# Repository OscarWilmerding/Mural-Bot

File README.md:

# Mural Bot
 Mural Painting Robot

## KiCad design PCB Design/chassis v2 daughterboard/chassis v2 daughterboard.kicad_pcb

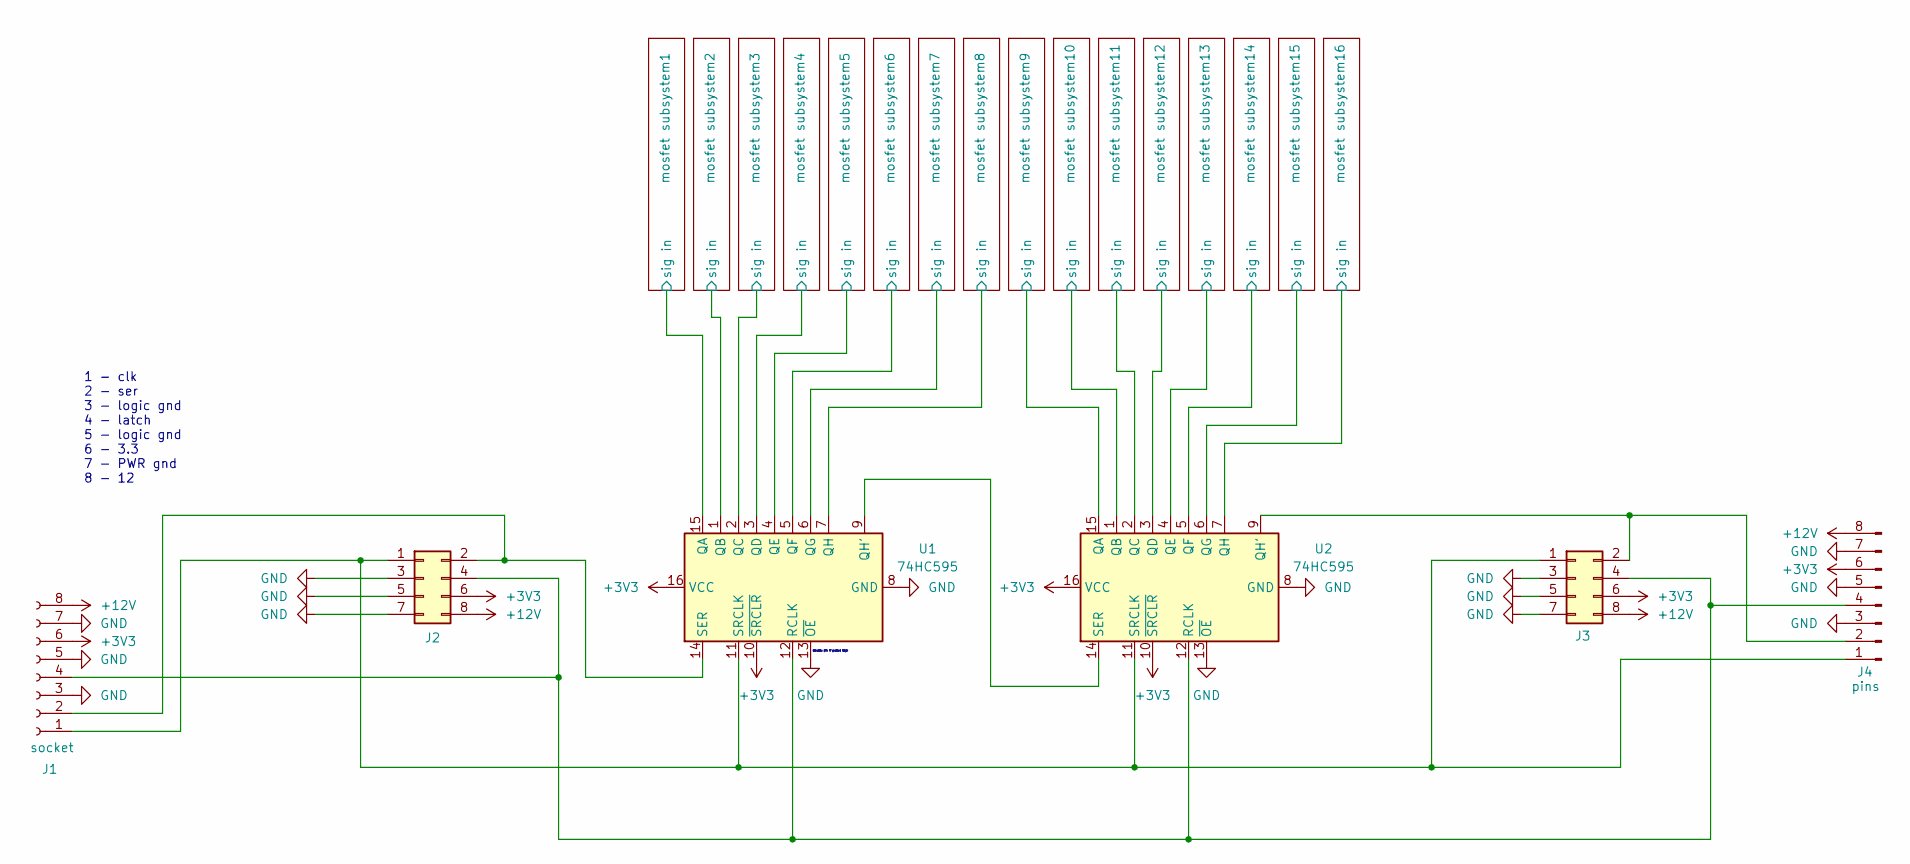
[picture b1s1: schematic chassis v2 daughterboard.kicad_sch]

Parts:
J1: socket; reversed socket connector
J2, J3: Conn_02x04_Odd_Even; PinHeader_2x04_P2.54mm_Vertical
J4: pins; reversed pin connector
U1, U2: 74HC595; DIP254P762X420-16

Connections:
+3V3: J1.6, J2.6, J3.6, J4.6, U1.10 (~SRCLR), U1.16 (VCC), U2.10 (~SRCLR), U2.16 (VCC)
+12V: J1.8, J2.8, J3.8, J4.8; also elsewhere on the board
/mosfet subsystem1/sig in: U1.15 (QA); also elsewhere on the board
/mosfet subsystem2/sig in: U1.1 (QB); also elsewhere on the board
/mosfet subsystem3/sig in: U1.2 (QC); also elsewhere on the board
/mosfet subsystem4/sig in: U1.3 (QD); also elsewhere on the board
/mosfet subsystem5/sig in: U1.4 (QE); also elsewhere on the board
/mosfet subsystem6/sig in: U1.5 (QF); also elsewhere on the board
/mosfet subsystem7/sig in: U1.6 (QG); also elsewhere on the board
/mosfet subsystem8/sig in: U1.7 (QH); also elsewhere on the board
/mosfet subsystem9/sig in: U2.15 (QA); also elsewhere on the board
/mosfet subsystem10/sig in: U2.1 (QB); also elsewhere on the board
/mosfet subsystem11/sig in: U2.2 (QC); also elsewhere on the board
/mosfet subsystem12/sig in: U2.3 (QD); also elsewhere on the board
/mosfet subsystem13/sig in: U2.4 (QE); also elsewhere on the board
/mosfet subsystem14/sig in: U2.5 (QF); also elsewhere on the board
/mosfet subsystem15/sig in: U2.6 (QG); also elsewhere on the board
/mosfet subsystem16/sig in: U2.7 (QH); also elsewhere on the board
GND: J1.3, J1.5, J1.7, J2.3, J2.5, J2.7, J3.3, J3.5, J3.7, J4.3, J4.5, J4.7, U1.8 (GND), U1.13 (~OE), U2.8 (GND), U2.13 (~OE); also elsewhere on the board
unnamed: J1.1, J2.1, J3.1, J4.1, U1.11 (SRCLK), U2.11 (SRCLK)
unnamed: J1.2, J2.2, U1.14 (SER)
unnamed: J1.4, J2.4, J3.4, J4.4, U1.12 (RCLK), U2.12 (RCLK)
unnamed: J3.2, J4.2, U2.9 (QH')
unnamed: U1.9 (QH'), U2.14 (SER)

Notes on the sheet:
1 - clk 2 - ser 3 - logic gnd 4 - latch 5 - logic gnd 6 - 3.3 7 - PWR gnd 8 - 12
disable pin if pulled high

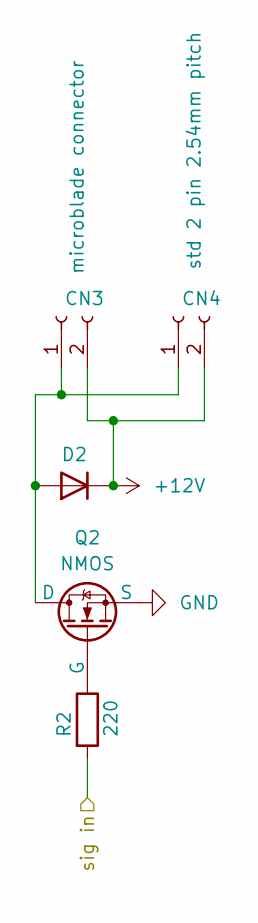
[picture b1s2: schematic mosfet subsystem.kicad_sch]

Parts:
CN3: microblade connector; modified jst zh used
CN4: std 2 pin 2.54mm pitch; clean 01x02 header
D2: D; D_SOD-123F
Q2: NMOS; Big Mosfet Old Style
R2: 220; R_2010_5025Metric_Pad1.40x2.65mm_HandSolder

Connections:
+12V: CN3.2, CN4.2, D2.1 (K); also elsewhere on the board
/mosfet subsystem2/sig in: R2.2; also elsewhere on the board
GND: Q2.3 (S); also elsewhere on the board
unnamed: CN3.1, CN4.1, D2.2 (A), Q2.2 (D)
unnamed: Q2.1 (G), R2.1

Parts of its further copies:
CN1, CN5, CN7, CN9, CN11, CN13, CN15, CN17, CN19, CN21, CN23, CN25, CN27, CN29, CN31: microblade connector; modified jst zh used
CN2, CN6, CN8, CN10, CN12, CN14, CN16, CN18, CN20, CN22, CN24, CN26, CN28, CN30, CN32: std 2 pin 2.54mm pitch; clean 01x02 header
D1, D3, D4, D5, D6, D7, D8, D9, D10, D11, D12, D13, D14, D15, D16: D; D_SOD-123F
Q1, Q3, Q4, Q5, Q6, Q7, Q8, Q9, Q10, Q11, Q12, Q13, Q14, Q15, Q16: NMOS; Big Mosfet Old Style
R1, R3, R4, R5, R6, R7, R8, R9, R10, R11, R12, R13, R14, R15, R16: 220; R_2010_5025Metric_Pad1.40x2.65mm_HandSolder

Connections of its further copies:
+12V: CN1.2, CN2.2, CN5.2, CN6.2, CN7.2, CN8.2, CN9.2, CN10.2, CN11.2, CN12.2, CN13.2, CN14.2, CN15.2, CN16.2, CN17.2, CN18.2, CN19.2, CN20.2, CN21.2, CN22.2, CN23.2, CN24.2, CN25.2, CN26.2, CN27.2, CN28.2, CN29.2, CN30.2, CN31.2, CN32.2, D1.1 (K), D3.1 (K), D4.1 (K), D5.1 (K), D6.1 (K), D7.1 (K), D8.1 (K), D9.1 (K), D10.1 (K), D11.1 (K), D12.1 (K), D13.1 (K), D14.1 (K), D15.1 (K), D16.1 (K); also elsewhere on the board
/mosfet subsystem1/sig in: R1.2; also elsewhere on the board
/mosfet subsystem3/sig in: R3.2; also elsewhere on the board
/mosfet subsystem4/sig in: R4.2; also elsewhere on the board
/mosfet subsystem5/sig in: R5.2; also elsewhere on the board
/mosfet subsystem6/sig in: R6.2; also elsewhere on the board
/mosfet subsystem7/sig in: R7.2; also elsewhere on the board
/mosfet subsystem8/sig in: R8.2; also elsewhere on the board
/mosfet subsystem9/sig in: R9.2; also elsewhere on the board
/mosfet subsystem10/sig in: R10.2; also elsewhere on the board
/mosfet subsystem11/sig in: R11.2; also elsewhere on the board
/mosfet subsystem12/sig in: R12.2; also elsewhere on the board
/mosfet subsystem13/sig in: R13.2; also elsewhere on the board
/mosfet subsystem14/sig in: R14.2; also elsewhere on the board
/mosfet subsystem15/sig in: R15.2; also elsewhere on the board
/mosfet subsystem16/sig in: R16.2; also elsewhere on the board
GND: Q1.3 (S), Q3.3 (S), Q4.3 (S), Q5.3 (S), Q6.3 (S), Q7.3 (S), Q8.3 (S), Q9.3 (S), Q10.3 (S), Q11.3 (S), Q12.3 (S), Q13.3 (S), Q14.3 (S), Q15.3 (S), Q16.3 (S); also elsewhere on the board
unnamed: CN1.1, CN2.1, D1.2 (A), Q1.2 (D)
unnamed: CN5.1, CN6.1, D3.2 (A), Q3.2 (D)
unnamed: CN7.1, CN8.1, D4.2 (A), Q4.2 (D)
unnamed: CN9.1, CN10.1, D5.2 (A), Q5.2 (D)
unnamed: CN11.1, CN12.1, D6.2 (A), Q6.2 (D)
unnamed: CN13.1, CN14.1, D7.2 (A), Q7.2 (D)
unnamed: CN15.1, CN16.1, D8.2 (A), Q8.2 (D)
unnamed: CN17.1, CN18.1, D9.2 (A), Q9.2 (D)
unnamed: CN19.1, CN20.1, D10.2 (A), Q10.2 (D)
unnamed: CN21.1, CN22.1, D11.2 (A), Q11.2 (D)
unnamed: CN23.1, CN24.1, D12.2 (A), Q12.2 (D)
unnamed: CN25.1, CN26.1, D13.2 (A), Q13.2 (D)
unnamed: CN27.1, CN28.1, D14.2 (A), Q14.2 (D)
unnamed: CN29.1, CN30.1, D15.2 (A), Q15.2 (D)
unnamed: CN31.1, CN32.1, D16.2 (A), Q16.2 (D)
unnamed: Q1.1 (G), R1.1
unnamed: Q3.1 (G), R3.1
unnamed: Q4.1 (G), R4.1
unnamed: Q5.1 (G), R5.1
unnamed: Q6.1 (G), R6.1
unnamed: Q7.1 (G), R7.1
unnamed: Q8.1 (G), R8.1
unnamed: Q9.1 (G), R9.1
unnamed: Q10.1 (G), R10.1
unnamed: Q11.1 (G), R11.1
unnamed: Q12.1 (G), R12.1
unnamed: Q13.1 (G), R13.1
unnamed: Q14.1 (G), R14.1
unnamed: Q15.1 (G), R15.1
unnamed: Q16.1 (G), R16.1

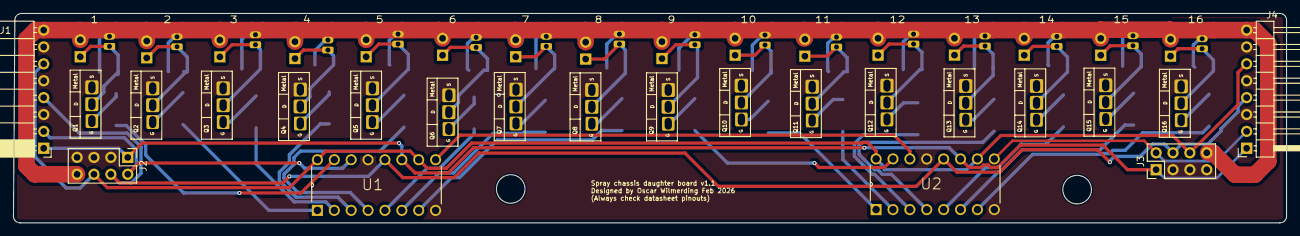
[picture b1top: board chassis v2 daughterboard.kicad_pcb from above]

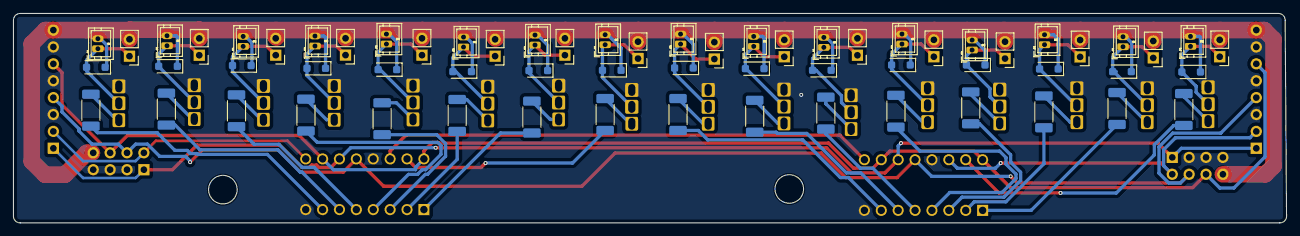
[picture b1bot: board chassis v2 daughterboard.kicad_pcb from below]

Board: 2 copper layers, 191.5 x 31.5 mm, 86 parts (64 on the bottom side), 56 nets.

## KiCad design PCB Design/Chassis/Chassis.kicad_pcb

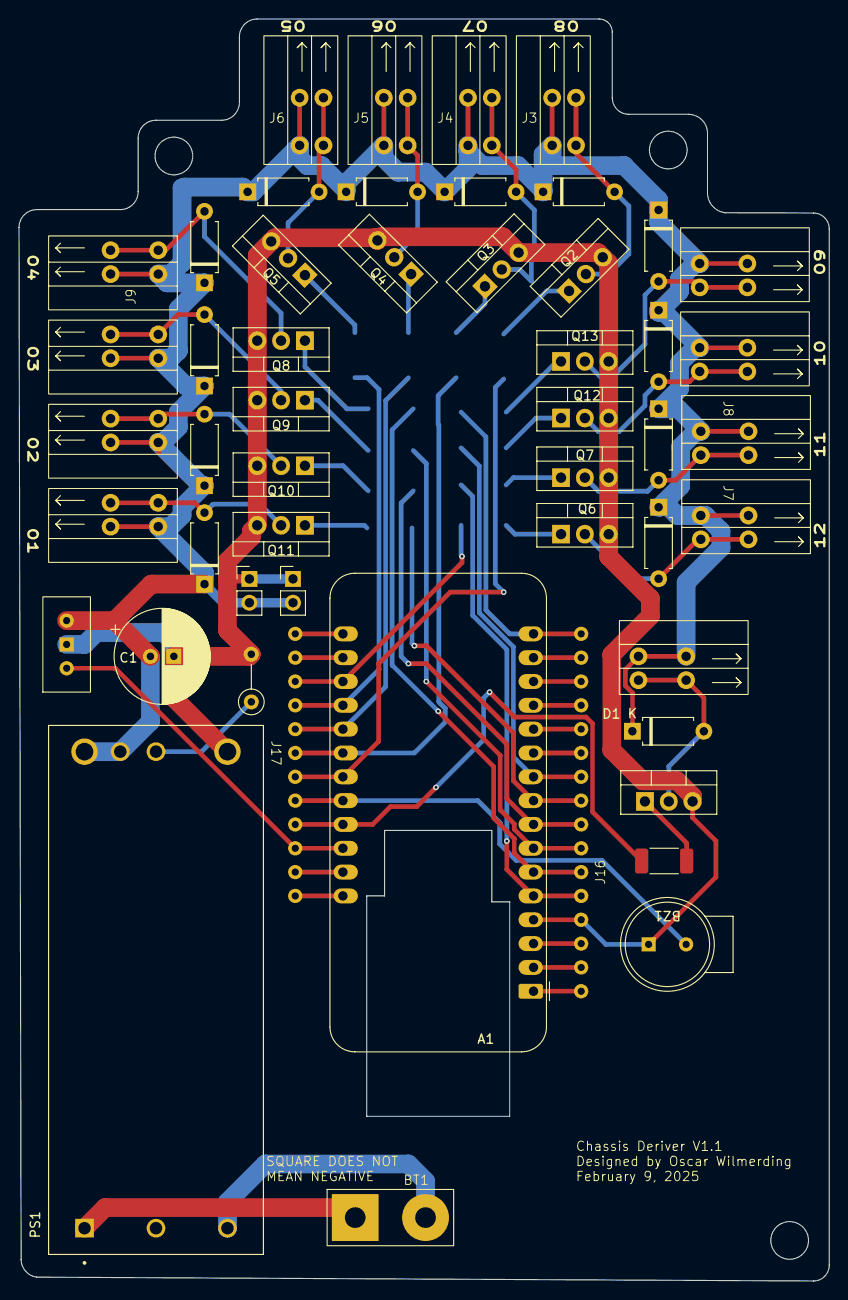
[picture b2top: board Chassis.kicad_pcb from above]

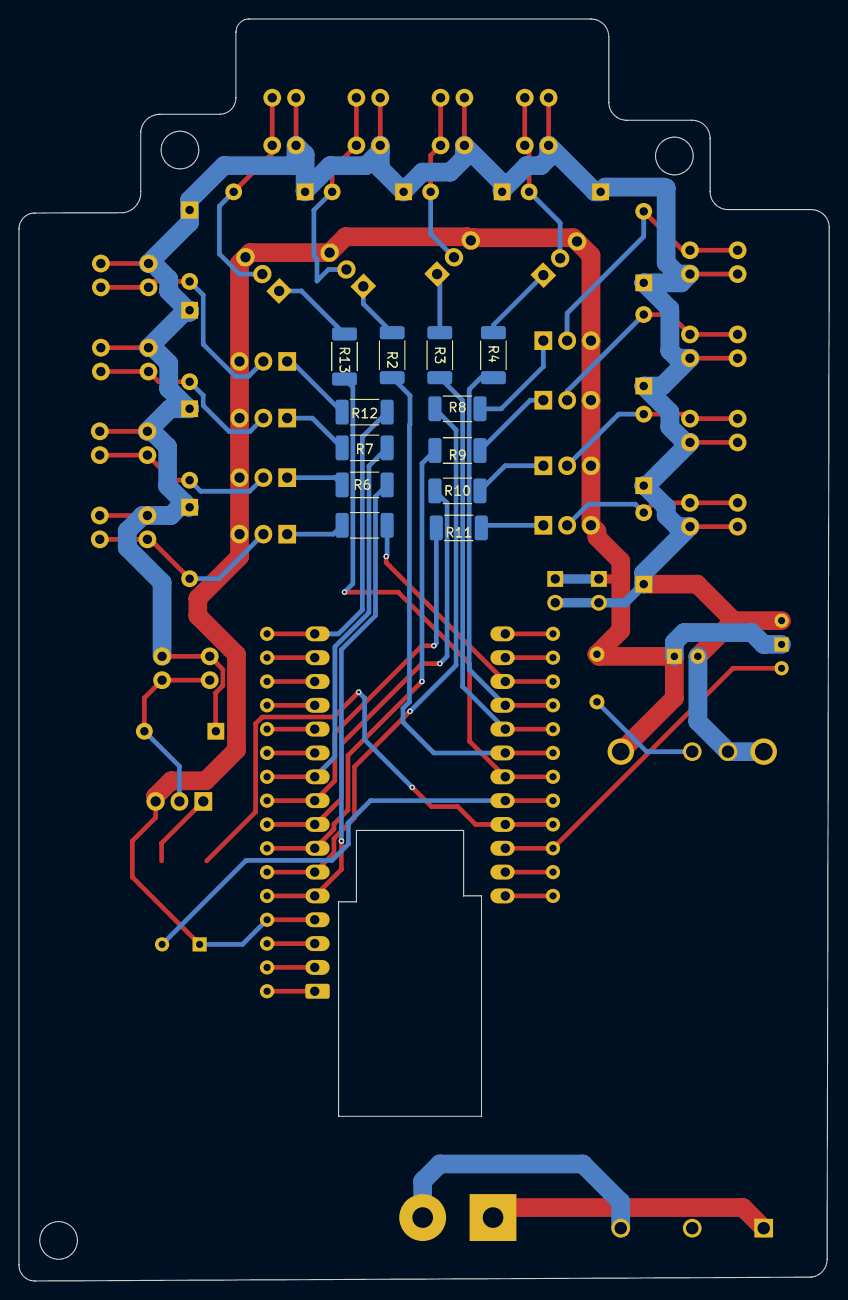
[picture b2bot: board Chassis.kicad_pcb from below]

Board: 2 copper layers, 86.4 x 134.5 mm, 63 parts (12 on the bottom side), 58 nets.

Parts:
A1: Adafruit_Feather_Generic; Adafruit_Feather
BT1: Battery_Cell; Ec5 pigtail
BZ1: Buzzer; buzzer
C1: 470uf; CP_Radial_D10.0mm_P2.50mm
D1, D2, D3, D4, D5, D6, D7, D8, D9, D10, D11, D12, D13: D; D_A-405_P7.62mm_Horizontal
J1: 5V voltage regulator; 5v voltage regulator
J2, J3, J4, J5, J6, J7, J8, J9, J10, J11, J12, J13, J15: Conn_01x02; 2 pin qwik connector
J14, J18: Conn_01x02; PinHeader_1x02_P2.54mm_Vertical
J16: microcontroller extension header; simple 01x06
J17: Microcontroller extension header; simple 01x12
PS1: RPMGE12-10; CONV_RPMGE12-10
Q1, Q2, Q3, Q4, Q5, Q6, Q7, Q8, Q9, Q10, Q11, Q12, Q13: NMOS; TO-220-3_Vertical
R1, R2, R3, R4, R5, R6, R7, R8, R9, R10, R11, R12, R13: 220; R_2010_5025Metric_Pad1.40x2.65mm_HandSolder
R14: R; R_Axial_DIN0207_L6.3mm_D2.5mm_P5.08mm_Vertical

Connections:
unnamed: A1.2 (3V3), J16.2
unnamed: A1.5 (A0), J16.5, R7.2
unnamed: A1.6 (A1), J16.6, R8.2
unnamed: A1.7 (A2), J16.7, R9.2
unnamed: A1.8 (A3), J16.8, R10.2
unnamed: A1.9 (A4), J16.9, R11.2
unnamed: A1.10 (A5), J16.10, R12.2
unnamed: A1.3 (AREF), J16.3
unnamed: A1.19 (D0), J17.19, R6.2
unnamed: A1.20 (D1), J17.20, R5.2
unnamed: A1.21 (D2), J17.21, R4.2
unnamed: A1.22 (D3), J17.22, R3.2
unnamed: A1.23 (D4), J17.23, R2.2
unnamed: A1.24 (D5), BZ1.1 (+), J17.24
unnamed: A1.25 (D6), J17.25, R1.2
unnamed: A1.27 (EN), J17.27
unnamed: A1.13 (MISO), J16.13
unnamed: A1.12 (MOSI), J16.12
unnamed: A1.14 (RX), J16.14
unnamed: A1.11 (SCK), J16.11
unnamed: A1.18 (SCL), J17.18
unnamed: A1.17 (SDA), J17.17
unnamed: A1.16 (SPARE), J16.16, R13.2
unnamed: A1.15 (TX), J16.15
unnamed: A1.26 (USB), J1.1, J17.26
unnamed: A1.28 (VBAT), J17.28
unnamed: A1.1 (~RESET), J16.1
unnamed: BT1.1 (+), PS1.1 (+VIN)
unnamed: BT1.2 (-), PS1.3 (-VIN)
unnamed: D1.2 (A), J2.1, Q1.2 (D)
unnamed: D2.2 (A), J3.1, Q2.2 (D)
unnamed: D3.2 (A), J4.1, Q3.2 (D)
unnamed: D4.2 (A), J5.1, Q4.2 (D)
unnamed: D5.2 (A), J6.1, Q5.2 (D)
unnamed: D6.2 (A), J7.1, Q6.2 (D)
unnamed: D7.2 (A), J8.1, Q7.2 (D)
unnamed: D8.2 (A), J9.1, Q8.2 (D)
unnamed: D9.2 (A), J10.1, Q9.2 (D)
unnamed: D10.2 (A), J11.1, Q10.2 (D)
unnamed: D11.2 (A), J12.1, Q11.2 (D)
unnamed: D12.2 (A), J13.1, Q12.2 (D)
unnamed: D13.2 (A), J15.1, Q13.2 (D)
unnamed: PS1.5 (TRIM), R14.1
unnamed: Q1.1 (G), R1.1
unnamed: Q2.1 (G), R2.1
unnamed: Q3.1 (G), R3.1
unnamed: Q4.1 (G), R4.1
unnamed: Q5.1 (G), R5.1
unnamed: Q6.1 (G), R6.1
unnamed: Q7.1 (G), R7.1
unnamed: Q8.1 (G), R8.1
unnamed: Q9.1 (G), R9.1
unnamed: Q10.1 (G), R10.1
unnamed: Q11.1 (G), R11.1
unnamed: Q12.1 (G), R12.1
unnamed: Q13.1 (G), R13.1
gnd: A1.4 (GND), BZ1.2 (-), C1.2, J1.2, J14.1, J16.4, J18.1, PS1.4 (-VOUT), Q1.3 (S), Q2.3 (S), Q3.3 (S), Q4.3 (S), Q5.3 (S), Q6.3 (S), Q7.3 (S), Q8.3 (S), Q9.3 (S), Q10.3 (S), Q11.3 (S), Q12.3 (S), Q13.3 (S), R14.2
pos: C1.1, D1.1 (K), D2.1 (K), D3.1 (K), D4.1 (K), D5.1 (K), D6.1 (K), D7.1 (K), D8.1 (K), D9.1 (K), D10.1 (K), D11.1 (K), D12.1 (K), D13.1 (K), J1.3, J2.2, J3.2, J4.2, J5.2, J6.2, J7.2, J8.2, J9.2, J10.2, J11.2, J12.2, J13.2, J14.2, J15.2, J18.2, PS1.6 (+SENSE), PS1.7 (+VOUT)

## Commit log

2025-01-25 Initial Comit
    eat beans and accomplish your dreams
2025-01-25 chatgpt updates towards velocity
    untested dont use this version, mostly checking is pushing is working
2025-01-25 small changes
    untested
2025-01-25 Update arduino_gcode_driver_v2.ino
    getting close to a usable version but still need to put in velocity equation
2025-01-25 velocity math theoretically implemented
    untested but the equations are in the maple file and should be poperly in the code, no debugging in code yet expecting a significant amount needed.
2025-01-26 Velocity equation run in 60us tops
    this is fast enough for my use case
2025-01-26 Velocity equations added, compiled fully
    untested, will be testing soon
2025-01-27 negligible changes
    negligible changes
2025-01-27 done during testing velocity
2025-01-28 MVP velocity features still kinda buggy
2025-01-28 got initial movement to the start of velocity working
    still needs work
2025-01-31 added debugging serial tools
2025-01-31 for visualizing geometry without math
2025-01-31 misc
2025-01-31 fixing drifting bug
    changing velocity calc to be in steps per ser not meters per sec there is weird rounding happening in code resilting in a side velocity being marginally larger than b side velocity
2025-01-31 bug report
    through some testing i think that rounding withi the code is not the greater cause of the drifting thats happening
2025-01-31 new velocity calculation approach
    this one should be moving more accurately and should be avoiding the approach infinity by reiman sum problem im having
2025-01-31 new velocity equations
    working equations I think this is moving RIGHT wooooo still need to test how straight the lines are though might do it with light painting
2025-02-01 Reformatting for organization
    proper velocity control should be in order for this
2025-02-03 File Reorganization
2025-02-03 implementing long string sending
    this is so I can send the long string of data to the chassis relating to where pixels are going to be during the movement. needs to be complicated because espnow limits data packet size to 250 bytes/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
2025-02-04 added large string transmission
    working and tested large string transmission on both ends (main and gcode driver)
2025-02-04 Initial Comit Gcode Generator
2025-02-04 implemented gcode for multi color
    added a new dropdown menu for slicing options
2025-02-05 major chassis pcb development
2025-02-05 pcb progress
2025-02-12 Create solenoid_testing.ino
    upgraded solenoid testig code
2025-02-12 pcb changes
2025-02-15 added comands for solenoid control
    did testing and i finally got some ok dots making a rig for more control now
2025-02-16 small change to solenoid script
    more real application func
2025-02-20 misc changes
2025-03-07 adding forgotten files
2025-03-12 updates to model and chassis script
2025-03-13 untested changes, some steps backwards
    this shit is hard making big changes and ik theres gonna be bugs
2025-03-16 got stripe communication working!!!
    processing for stripe is yet to be done
2025-03-16 slight fix
2025-03-19 cad changes and quick pcb design
2025-03-19 changing communication and data processing
2025-03-19 typos n stuff
2025-03-20 massacring my poor boy
    a LOT of new features regarding how to read data that is fr not going to be working for a while
2025-03-21 getting logic sorted
    still fs unrunnable but fixing typos and getting the logic right, still need to fix a few things specifically get rid of 'pins' decleration in the beginning
2025-03-25 solidworks updates
2025-03-26 solidworks updates and renders
2025-04-05 yuge update
    got solenoids scheduled and responding to sent data
2025-04-05 modeling and gcode minor updates
2025-04-05 mostly working synchronously but needs testing
    time each side and make sure overall time is right and they start and end at the same time after this.
2025-04-14 quick save
2025-04-17 communication in a good state and gcode gen bug fixes
2025-04-18 small cad and button functionality for base
2025-07-18 bulk backup
2025-07-20 added calibration command to chassis
2025-07-23 cad updates
2025-08-12 Add Python serial GUIs and reorganize CAD files
    Added Python Tools for serial interfaces: 'Chassis Serial Interface.py', 'base module serial interface.py', and a startup script. Major CAD file reorganization: moved, renamed, and added files for V2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
2025-08-26 platformio switch
    hopefully this is the way forward
2025-08-26 bare minimum working upload
    still unable to read little fs gcode file
2025-08-26 4 corners command and adding chassis into platformio
2025-09-11 rand
2025-09-14 Add V4 Chassis CAD files and update Big Motor Base
2026-02-12 lots of changes
2026-02-12 saving shit before big big chassis code changes
2026-02-26 slicing update
    got rid of offset varaible, fixed issues related to number of nozzles in the row
2026-03-07 schematic has been changed but footprints on board are almost what they were at order
2026-03-26 stable somewhat
2026-03-27 stable microcontroller code
    pushing before i make fundamental change to spray and stripe functionality
2026-04-25 stable version
    missing pixel issue but technically works ig
2026-04-25 test change
